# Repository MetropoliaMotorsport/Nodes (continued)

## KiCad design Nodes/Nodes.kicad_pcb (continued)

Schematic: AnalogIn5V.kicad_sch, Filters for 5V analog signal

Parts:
C63, C68, C73, C78: 100nF; C_0805_2012Metric_Pad1.18x1.45mm_HandSolder; TOLERANCE (FILL IN AS +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 10%
C64, C65, C66, C67, C69, C70, C71, C72, C74, C75, C76, C77, C79, C80: 10nF; C_0805_2012Metric_Pad1.18x1.45mm_HandSolder; TOLERANCE (FILL IN AS +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 10%
L13, L14, L15, L16, L17, L18, L19, L20, L21, L22, L23, L24, L25, L26: 1uH; L_0805_2012Metric_Pad1.15x1.40mm_HandSolder; TOLERANCE 30%; CURRENT RATING 900mA
R65, R66, R75, R76, R85, R86, R95: 1kR; R_0805_2012Metric_Pad1.20x1.40mm_HandSolder
R67, R69, R77, R79, R87, R89, R98: DNA; R_0805_2012Metric_Pad1.20x1.40mm_HandSolder; PART NUMBER CRCW0805680RFKEA
R68, R70, R78, R80, R88, R90, R96: 1.74kR; R_0805_2012Metric_Pad1.20x1.40mm_HandSolder
R71, R72, R81, R82, R91, R92, R97: 10MR; R_0805_2012Metric_Pad1.20x1.40mm_HandSolder; POWER RATING 125mW; VOLTAGE RATING (DC) 150V
R73, R74, R83, R84, R93, R94, R99: 3.24kR; R_0805_2012Metric_Pad1.20x1.40mm_HandSolder
T12, T13, T14, T15, T16, T17, T18: Conn_01x01; TestPoint_THTPad_D1.5mm_Drill0.7mm
U6, U7, U8, U9: LM358BAIDR; FP-D0008A-IPC_A

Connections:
+24V: C63.1, C68.1, C73.1, C78.1, U6.8 (V+), U7.8 (V+), U8.8 (V+), U9.8 (V+); also elsewhere on the board
/AnalogNode/ADC2: C66.1, R68.2, R73.1, T12.1; also elsewhere on the board
/AnalogNode/ADC3: C67.1, R70.2, R74.1, T13.1; also elsewhere on the board
/AnalogNode/ADC4: C71.1, R78.2, R83.1, T14.1; also elsewhere on the board
/AnalogNode/ADC5: C72.1, R80.2, R84.1, T15.1; also elsewhere on the board
/AnalogNode/ADC6: C76.1, R88.2, R93.1, T16.1; also elsewhere on the board
/AnalogNode/ADC7: C77.1, R90.2, R94.1, T17.1; also elsewhere on the board
/AnalogNode/ADC8: C80.1, R96.2, R99.1, T18.1; also elsewhere on the board
AnIN5V_0: L13.1, R71.1; also elsewhere on the board
AnIN5V_1: L14.1, R72.1; also elsewhere on the board
AnIN5V_2: L17.1, R81.1; also elsewhere on the board
AnIN5V_3: L18.1, R82.1; also elsewhere on the board
AnIN5V_4: L21.1, R91.1; also elsewhere on the board
AnIN5V_5: L22.1, R92.1; also elsewhere on the board
AnIN5V_6: L25.1, R97.1; also elsewhere on the board
GND: C63.2, C64.2, C65.2, C66.2, C67.2, C68.2, C69.2, C70.2, C71.2, C72.2, C73.2, C74.2, C75.2, C76.2, C77.2, C78.2, C79.2, C80.2, R67.2, R69.2, R71.2, R72.2, R73.2, R74.2, R77.2, R79.2, R81.2, R82.2, R83.2, R84.2, R87.2, R89.2, R91.2, R92.2, R93.2, R94.2, R97.2, R98.2, R99.2, U6.4 (V-), U7.4 (V-), U8.4 (V-), U9.4 (V-); also elsewhere on the board
unnamed: L13.2, R65.1
unnamed: L14.2, R66.1
unnamed: L15.2, R68.1
unnamed: L16.2, R70.1
unnamed: L17.2, R75.1
unnamed: L18.2, R76.1
unnamed: L19.2, R78.1
unnamed: L20.2, R80.1
unnamed: L21.2, R85.1
unnamed: L22.2, R86.1
unnamed: L23.2, R88.1
unnamed: L24.2, R90.1
unnamed: L25.2, R95.1
unnamed: L26.2, R96.1
unnamed: C79.1, R95.2, R98.1, U6.3 (IN1+)
unnamed: L26.1, U6.1 (OUT1), U6.2 (IN1-)
unnamed: C65.1, R65.2, R67.1, U7.3 (IN1+)
unnamed: L15.1, U7.1 (OUT1), U7.2 (IN1-)
unnamed: C64.1, R66.2, R69.1, U7.5 (IN2+)
unnamed: L16.1, U7.6 (IN2-), U7.7 (OUT2)
unnamed: C70.1, R75.2, R77.1, U8.3 (IN1+)
unnamed: L19.1, U8.1 (OUT1), U8.2 (IN1-)
unnamed: C69.1, R76.2, R79.1, U8.5 (IN2+)
unnamed: L20.1, U8.6 (IN2-), U8.7 (OUT2)
unnamed: C75.1, R85.2, R87.1, U9.3 (IN1+)
unnamed: L23.1, U9.1 (OUT1), U9.2 (IN1-)
unnamed: C74.1, R86.2, R89.1, U9.5 (IN2+)
unnamed: L24.1, U9.6 (IN2-), U9.7 (OUT2)

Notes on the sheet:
When a 5000 step resolution is wanted and lower offset voltage => Use ADA4522-2 instead of LM358
If the ntc sensor connected, for example, to AnIN5V_0 => R65 and L13 shorted; R67=680 Ohm

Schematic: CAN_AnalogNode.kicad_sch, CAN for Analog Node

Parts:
C47, C48: 100nF; C_0805_2012Metric_Pad1.18x1.45mm_HandSolder; TOLERANCE (FILL IN AS +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 10%
C49: 4.7nF; C_0805_2012Metric_Pad1.18x1.45mm_HandSolder; TOLERANCE (FILL IN AS +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 10%
D4: ESDCAN24-2BLY; SOT95P255X125-3N; Mouser Part Number 511-ESDCAN24-2BLY
IC4: TCAN1462VDRQ1; SOIC127P600X175-8N; MANUFACTURER_PART_NUMBER TCAN1462VDRQ1; MOUSER PART NUMBER 595-TCAN1462VDRQ1
R37, R46, R47, R109: 120R; R_0805_2012Metric_Pad1.20x1.40mm_HandSolder
SW3: CAS-220TB1; SOP175P560X250-6N

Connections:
+5V: C47.1, IC4.3 (VCC); also elsewhere on the board
/AnalogNode/CANRx: IC4.4 (RXD); also elsewhere on the board
/AnalogNode/CANTx: IC4.1 (TXD); also elsewhere on the board
CANHI: D4.1 (I/O), IC4.7 (CANH), R37.1, R46.1; also elsewhere on the board
CANLO: D4.2 (I/O), IC4.6 (CANL), R47.2, R109.2; also elsewhere on the board
GND: C47.2, C48.2, C49.2, D4.3 (I/O), IC4.2 (GND), IC4.8 (STB); also elsewhere on the board
unnamed: C49.1, SW3.3 (C), SW3.4 (A)
unnamed: R37.2, R46.2, SW3.2 (B)
unnamed: R47.1, R109.1, SW3.5 (B)
VCC: C48.1, IC4.5 (NC_VIO); also elsewhere on the board

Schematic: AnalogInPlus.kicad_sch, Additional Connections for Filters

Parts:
J7, J8: HLE-104-02-L-DV-BE-A-P-TR; HLE-104-02-XXX-DV-BE-A-P-TR; MANUFACTURER_PART_NUMBER HLE-104-02-L-DV-BE-A-P-TR

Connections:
+24V: J7.5, J8.5; also elsewhere on the board
/AnalogNode/ADC9: J8.7; also elsewhere on the board
/AnalogNode/ADC10: J8.8; also elsewhere on the board
/AnalogNode/ADC11: J7.7; also elsewhere on the board
/AnalogNode/ADC12: J7.8; also elsewhere on the board
AnIN_0: J7.2; also elsewhere on the board
AnIN_1: J7.3; also elsewhere on the board
AnIN_2: J8.2; also elsewhere on the board
AnIN_3: J8.3; also elsewhere on the board
GND: J7.6, J8.6; also elsewhere on the board
PWR0: J7.4; also elsewhere on the board
PWR1: J7.1; also elsewhere on the board
PWR2: J8.4; also elsewhere on the board
PWR3: J8.1; also elsewhere on the board

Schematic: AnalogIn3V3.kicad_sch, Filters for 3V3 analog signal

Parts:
C81: 100nF; C_0805_2012Metric_Pad1.18x1.45mm_HandSolder; TOLERANCE (FILL IN AS +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 10%
C82, C83, C84, C85: 10nF; C_0805_2012Metric_Pad1.18x1.45mm_HandSolder; TOLERANCE (FILL IN AS +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 10%
L27, L28, L29, L30: 1uH; L_0805_2012Metric_Pad1.15x1.40mm_HandSolder; TOLERANCE 30%; CURRENT RATING 900mA
R100, R101, R102, R105: 1kR; R_0805_2012Metric_Pad1.20x1.40mm_HandSolder
R103, R104, R119, R120: DNA; R_0805_2012Metric_Pad1.20x1.40mm_HandSolder; PART NUMBER CRCW0805680RFKEA
R106, R107: 10MR; R_0805_2012Metric_Pad1.20x1.40mm_HandSolder; POWER RATING 125mW; VOLTAGE RATING (DC) 150V
T19, T20: Conn_01x01; TestPoint_THTPad_D1.5mm_Drill0.7mm
U10: LM358BAIDR; FP-D0008A-IPC_A

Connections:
+24V: C81.1, U10.8 (V+); also elsewhere on the board
/AnalogNode/ADC0: C85.1, R105.2, R119.1, T20.1; also elsewhere on the board
/AnalogNode/ADC1: C82.1, R102.2, R120.1, T19.1; also elsewhere on the board
AnIN3V3_0: L27.1, R106.1; also elsewhere on the board
AnIN3V3_1: L28.1, R107.1; also elsewhere on the board
GND: C81.2, C82.2, C83.2, C84.2, C85.2, R103.2, R104.2, R106.2, R107.2, R119.2, R120.2, U10.4 (V-); also elsewhere on the board
unnamed: L27.2, R100.1
unnamed: L28.2, R101.1
unnamed: L29.2, R105.1
unnamed: L30.2, R102.1
unnamed: C84.1, R100.2, R103.1, U10.3 (IN1+)
unnamed: L29.1, U10.1 (OUT1), U10.2 (IN1-)
unnamed: C83.1, R101.2, R104.1, U10.5 (IN2+)
unnamed: L30.1, U10.6 (IN2-), U10.7 (OUT2)

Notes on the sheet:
If the ntc sensor connected, for example, to AnIN3V3_0 => R100 and L27 shorted; R103=680 Ohm
When a 5000 step resolution is wanted and lower offset voltage => Use ADA4522-2 instead of LM358

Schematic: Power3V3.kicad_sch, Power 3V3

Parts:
C29: 100nF; C_0805_2012Metric_Pad1.18x1.45mm_HandSolder; TOLERANCE (FILL IN AS +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 10%
C30: 470nF; C_0805_2012Metric_Pad1.18x1.45mm_HandSolder
IC5: ST730MR; SOT95P280X145-5N; Mouser Part Number 511-ST730MR
LED13: SML-210YTT86M; LED_0805_2012Metric_Pad1.15x1.40mm_HandSolder; MANUFACTURER_PART_NUMBER SML-210YTT86M
R41: 300R; R_0805_2012Metric_Pad1.20x1.40mm_HandSolder; POWER RATING 400mW; TOLERANCE 5%
R42: 1MR; R_0805_2012Metric_Pad1.20x1.40mm_HandSolder
R43: 576kR; R_0805_2012Metric_Pad1.20x1.40mm_HandSolder
T5: Conn_01x01; TestPoint_THTPad_D1.5mm_Drill0.7mm

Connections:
+5V: C29.1, IC5.3 (VIN), IC5.5 (EN); also elsewhere on the board
GND: C29.2, C30.2, IC5.2 (GND), R41.2, R43.2; also elsewhere on the board
unnamed: IC5.4 (ADJ), R42.2, R43.1
unnamed: LED13.1 (K), R41.1
VCC: C30.1, IC5.1 (VOUT), LED13.2 (A), R42.1, T5.1; also elsewhere on the board

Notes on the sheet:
The circuit below is for an adjustable version (ST730MR). It is recommended to use a fixed voltage regulator (ST730M33R). In order for the circuit to be suitable for a fixed regulator, remove R42 and R43. Vout=1.2*(1+R42/R43)

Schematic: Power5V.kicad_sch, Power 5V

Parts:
C18: 2.2uF; C_0805_2012Metric_Pad1.18x1.45mm_HandSolder
C19: 100nF; C_0805_2012Metric_Pad1.18x1.45mm_HandSolder; TOLERANCE (FILL IN AS +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 10%
C23: 10uF; C_0805_2012Metric_Pad1.18x1.45mm_HandSolder
L5: 4.7uH; L_0805_2012Metric_Pad1.15x1.40mm_HandSolder
LED14: SML-H12P8TT86; LED_0805_2012Metric_Pad1.15x1.40mm_HandSolder; MANUFACTURER_PART_NUMBER SML-H12P8TT86; MOUSER PART NUMBER 755-SML-H12P8TT86
PS1: LMR50410YFQDBVRQ1; SOT95P280X145-6N; Mouser Part Number 595-MR50410YFQDBVRQ1
R44: 1kR; R_0805_2012Metric_Pad1.20x1.40mm_HandSolder
R48: 88.7kR; R_0805_2012Metric_Pad1.20x1.40mm_HandSolder
R49: 22.1kR; R_0805_2012Metric_Pad1.20x1.40mm_HandSolder
T7: Conn_01x01; TestPoint_THTPad_D1.5mm_Drill0.7mm

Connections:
+5V: C23.1, L5.2, LED14.2 (A), R48.2, T7.1; also elsewhere on the board
+24V: C18.1, PS1.4 (EN), PS1.5 (VIN); also elsewhere on the board
GND: C18.2, C23.2, PS1.2 (GND), R44.2, R49.2; also elsewhere on the board
unnamed: LED14.1 (K), R44.1
unnamed: C19.1, PS1.1 (CB)
unnamed: PS1.3 (FB), R48.1, R49.1
unnamed: C19.2, L5.1, PS1.6 (SW)

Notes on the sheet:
The circuit below is for an adjustable version (LMR50410YFQDBVRQ1). It is recommended to use a fixed voltage regulator (LMR50410Y5FQDBVRQ1). In order for the circuit to be suitable for a fixed regulator, it is necessary to connect the FB pin to the SW pin directly, so for this remove R49, and solde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

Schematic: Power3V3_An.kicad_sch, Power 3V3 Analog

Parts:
C31: 470nF; C_0805_2012Metric_Pad1.18x1.45mm_HandSolder
C32: 100nF; C_0805_2012Metric_Pad1.18x1.45mm_HandSolder; TOLERANCE (FILL IN AS +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 10%
IC6: ST730MR; SOT95P280X145-5N; Mouser Part Number 511-ST730MR
LED15: 150080BS75000; LED_0805_2012Metric_Pad1.15x1.40mm_HandSolder; MANUFACTURER_PART_NUMBER SZYY0805B
R35: 10mR; R_0805_2012Metric_Pad1.20x1.40mm_HandSolder; TOLERANCE 1%
R38: 300R; R_0805_2012Metric_Pad1.20x1.40mm_HandSolder; POWER RATING 400mW; TOLERANCE 5%
R39: 1MR; R_0805_2012Metric_Pad1.20x1.40mm_HandSolder
R40: 576kR; R_0805_2012Metric_Pad1.20x1.40mm_HandSolder
T8, T23: Conn_01x01; TestPoint_THTPad_D1.5mm_Drill0.7mm

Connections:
+5V: C32.1, IC6.3 (VIN); also elsewhere on the board
ADC: IC6.1 (VOUT), R35.2, R39.1, T23.1; also elsewhere on the board
EN: IC6.5 (EN); also elsewhere on the board
GND: C31.2, C32.2, IC6.2 (GND), R38.2, R40.2; also elsewhere on the board
unnamed: IC6.4 (ADJ), R39.2, R40.1
unnamed: LED15.1 (K), R38.1
VCCA: C31.1, LED15.2 (A), R35.1, T8.1; also elsewhere on the board

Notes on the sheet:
The circuit below is for an adjustable version (ST730MR). It is recommended to use a fixed voltage regulator (ST730M33R). In order for the circuit to be suitable for a fixed regulator, remove R39 and R40. Vout=1.2*(1+R39/R40)

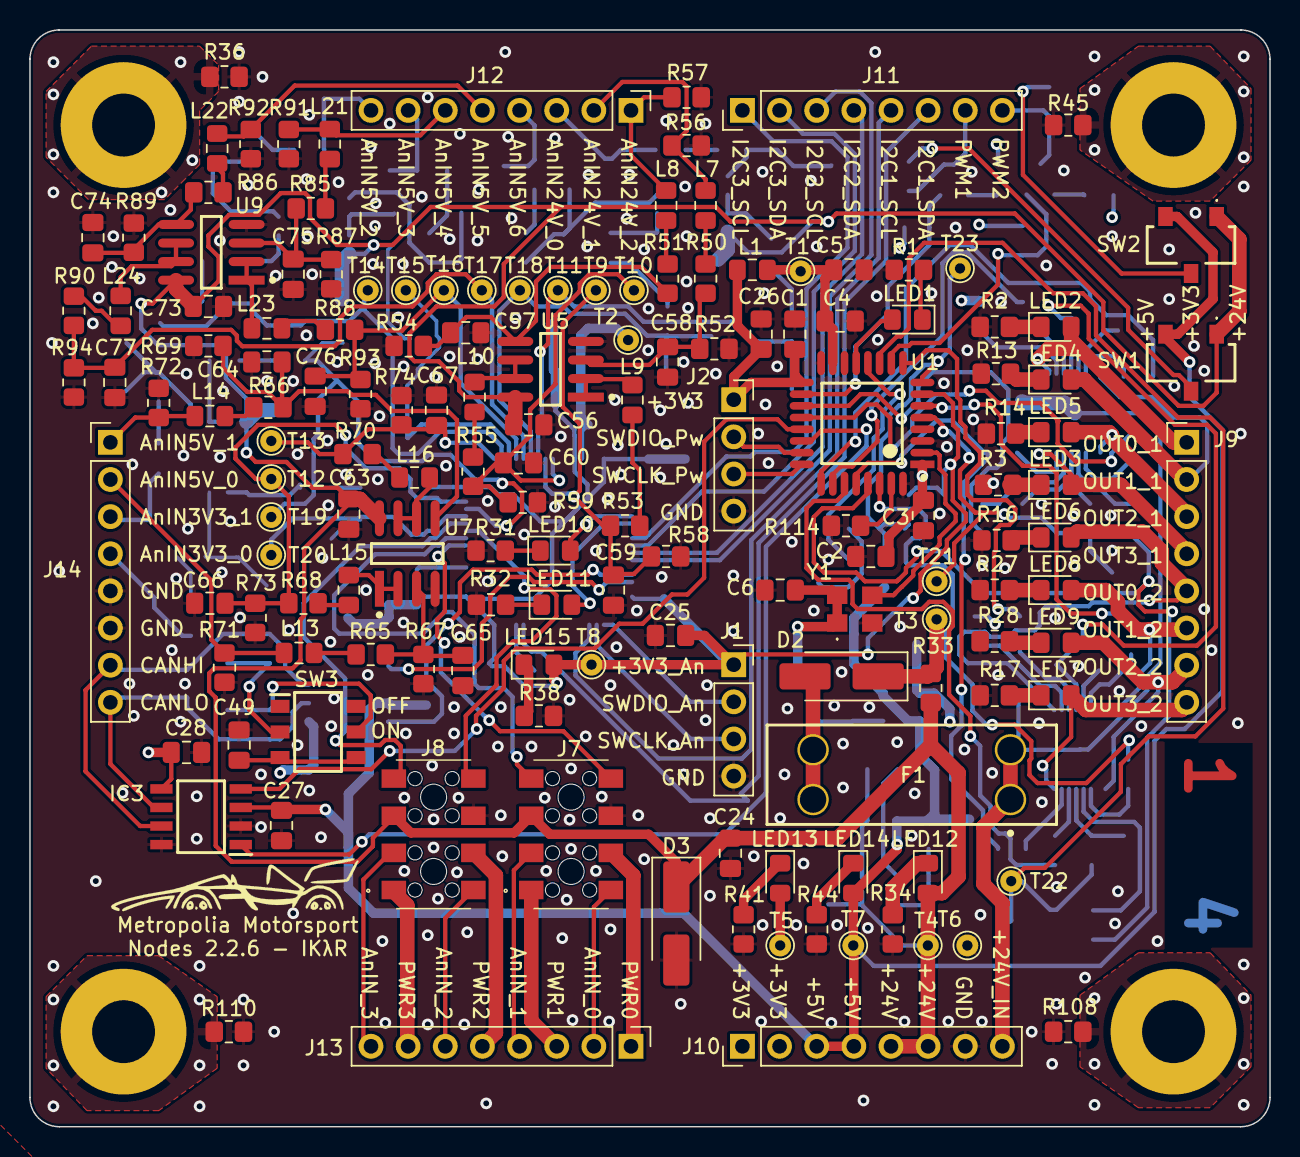
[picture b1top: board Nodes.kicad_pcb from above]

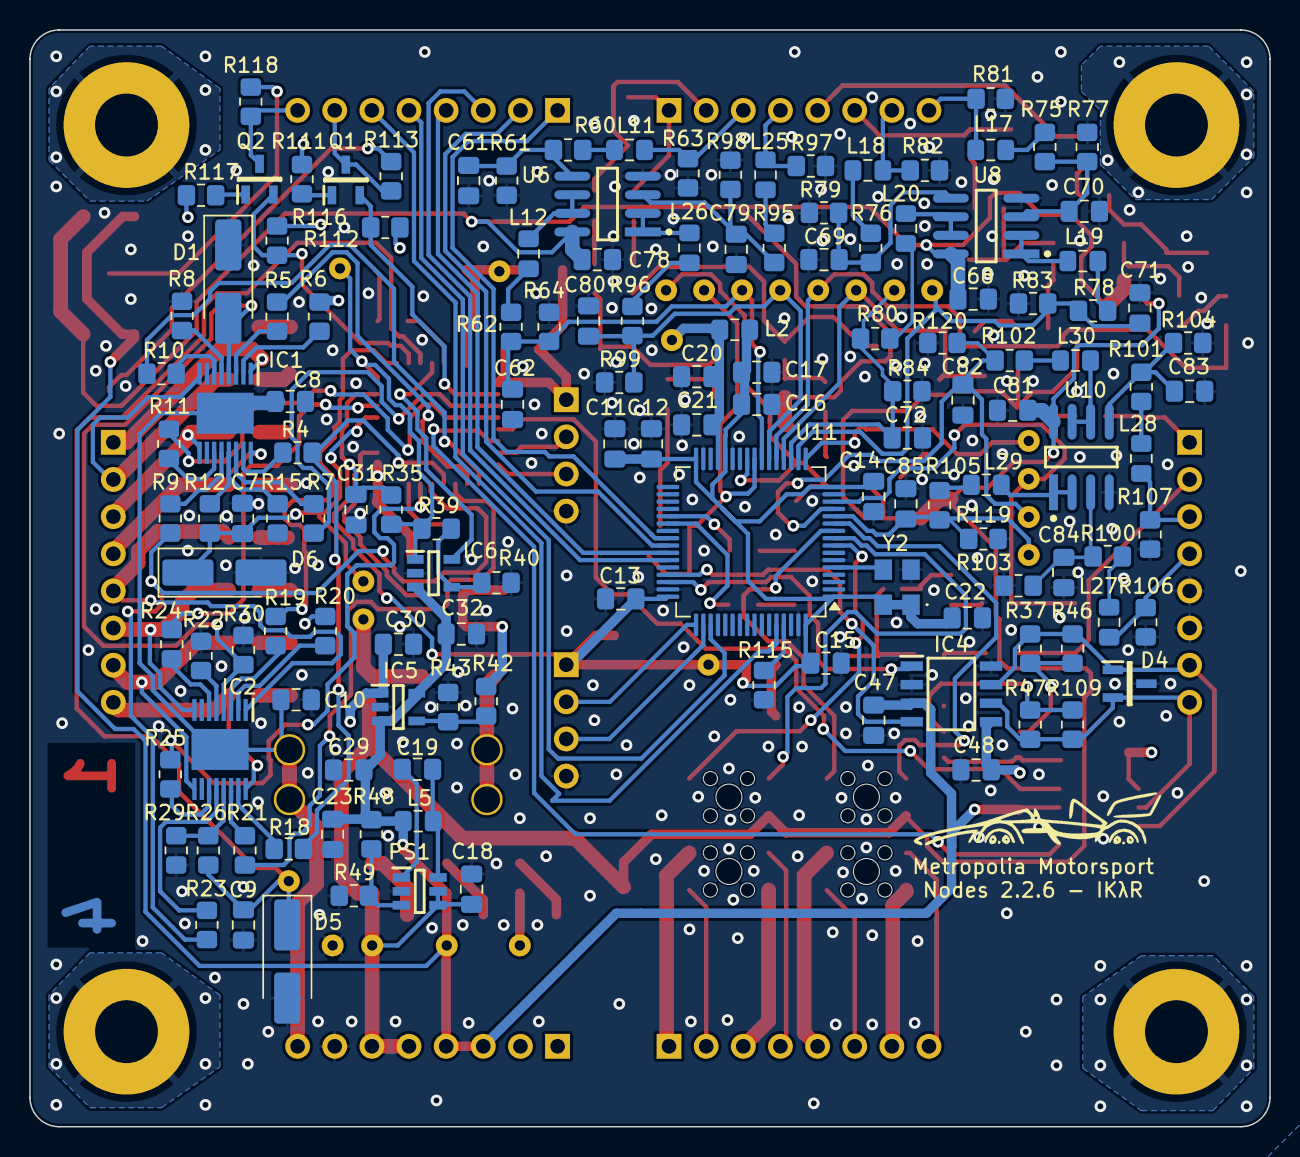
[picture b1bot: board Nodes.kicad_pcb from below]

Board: 4 copper layers, 84.8 x 75.0 mm, 293 parts (138 on the bottom side), 193 nets.

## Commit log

2024-06-08 First commit v2.11
2024-06-13 Nodes v2.1.2
    -Added power switch
    - Changed footprints to handsolder for small components
    - Can numbering changed 1->2 and 2->1
    - Some components have been changed
    - Some small changes with texts
    - Improved BOM
2024-06-17 Nodes v2.1.2 Improved
    - Improved schematic design
    - Added two 4.7 uF caps according to the datasheets of the microchips
    - Other small changes
2024-06-21 Nodes v2.2
    - This version not compatible with BOB v.2.1.2 and older!
    - Completely new layout design
    - New power supply system with new voltage regulators
    - New microchip STM32G431RBTx for the Analog Node
    - New connection system (instead of 18 pin headers now 8 pin and pins were grouped by functions)
    - Reduced size of the board by 5%
2024-06-22 Nodes v2.2 Improved
    - J9 connector moved by 0.2 mm to the left
    - Same changes as older version, but, please DO NOT PRINT OLDER V2.2 WITHOUT APPROVE
2024-07-10 Nodes v2.2.2
    - Level-Shifter on PWM1 for 24V applications added
2024-07-10 Nodes v2.2.2
    - Level-Shifter on PWM1 for 24V applications added
    - BOM generated
    - GBR and DRL files generated
2024-08-13 Nodes v2.2.3
    - Added one more PWM Level shifter
    - Controllable amplitude of PWM by switches
    - Added labels
    - Added resistors to solve BOOT issue
    - I2C1 pins changed
    - More GND vias
2024-08-30 Nodes v2.2.4
    - Added two Zener Diodes for CS pins of High-Side drivers
2024-09-19 Nodes v2.2.5
    - New High-Side Driver (Same footprint, just new info)
    - Two resistors added for 3V3 Filters, which can be used to implement voltage divider
2024-10-23 Nodes 2.2.5 Revision 1
    - New LED colour coding
    - Nodes Datasheet added
2024-12-06 Nodes v2.2.6 Revision 1.1
    - CAN connection mistake for Analog Node was fixed
    - Updated datasheet about CAN
